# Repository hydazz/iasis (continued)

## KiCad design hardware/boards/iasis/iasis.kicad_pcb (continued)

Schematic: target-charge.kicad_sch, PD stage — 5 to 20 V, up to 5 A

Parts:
C1330, C1331, C1332, C1333, C1336, C1337, C1338, C1339: 10u 50V X7R; C_1210_3225Metric; MPN CL32B106KBJNNNE; LCSC C138687
C1334: 100u 35V; CP_Elec_6.3x7.7; MPN HBO101M1VTR-0608; LCSC C3031628
C1335, C1340, C1347, C1348: 100n 50V X7R; C_0402_1005Metric; MPN CL05B104KB54PNC; LCSC C307331
C1341, C1342: 100n; C_0402_1005Metric; MPN CL05B104KO5NNNC; LCSC C1525
C1343: 10u 16V X5R; C_0805_2012Metric; MPN CL21A106KAYNNNE; LCSC C15850
C1344: 10n; C_0402_1005Metric; MPN CL05B103KB5NNNC; LCSC C15195
C1345: 4.7n; C_0402_1005Metric; MPN 0402B472K500NT; LCSC C1538
C1346: 100p C0G; C_0402_1005Metric; MPN 0402CG101J500NT; LCSC C1546
L1330: 4.7u; L_Changjiang_FXL1050; MPN AAPS1050M4R7A; LCSC C54425770
NT1330: NetTie_2; NetTie-2_SMD_Pad0.5mm
Q1330, Q1331: TMGN4060DF; Vishay_PowerPAK_1212-8_Single; MPN TMGN4060DF; LCSC C7422903
Q1332, Q1333: SP60N05GNJ; Vishay_PowerPAK_1212-8_Single; MPN SP60N05GNJ; LCSC C22466768
Q1334: 2N7002; SOT-23; MPN 2N7002; LCSC C8545
R1330: 1; R_0402_1005Metric; MPN 0402WGF100KTCE; LCSC C25086
R1331, R1332, R1336: 47k 1%; R_0402_1005Metric; MPN 0402WGF4702TCE; LCSC C25792
R1333: 56k 1%; R_0402_1005Metric; MPN 0402WGF5602TCE; LCSC C25796
R1334: 10m 1%; R_1206_3216Metric; MPN RLM12FTCMR010; LCSC C188070
R1335: 200k 1%; R_0402_1005Metric; MPN 0402WGF2003TCE; LCSC C25764
R1337: 15k 1%; R_0402_1005Metric; MPN 0402WGF1502TCE; LCSC C25756
R1338, R1339: 100k; R_0402_1005Metric; MPN 0402WGF1003TCE; LCSC C25741
U1330: TPS55288RPMR; TI_RPM0026A; MPN TPS55288RPMR; LCSC C2864583
U1331: LM74502DDFR; Texas_DDF0008A_SOT-8_1.6x2.9mm_P0.65mm; MPN LM74502DDFR; LCSC C3236215

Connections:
5V_LOGIC: R1330.1; also elsewhere on the board
/Target ports/Target 2/Output and charging/CHARGE_EN: R1339.1, U1331.1 (EN); also elsewhere on the board
/Target ports/Target 2/Output and charging/Charging stage/CONV: C1334.1, C1347.2, C1348.1, Q1332.5 (D), R1334.2, R1335.1, U1330.13 (ISN), U1331.5 (VS)
/Target ports/Target 2/Output and charging/Charging stage/OUT_GATE: Q1332.4 (G), Q1333.4 (G), U1331.6 (GATE)
/Target ports/Target 2/Output and charging/Charging stage/OUT_OV: R1335.2, R1336.1, R1337.1, U1331.7 (OV)
/Target ports/Target 2/Output and charging/Charging stage/OUT_SRC: Q1332.1 (S), Q1332.2 (S), Q1332.3 (S), Q1333.1 (S), Q1333.2 (S), Q1333.3 (S), U1331.8 (SRC)
/Target ports/Target 2/Output and charging/Charging stage/STAGE_AGND: C1344.2, C1345.2, C1346.2, NT1330.2, R1331.2, R1332.2, U1330.10 (AGND)
/Target ports/Target 2/Output and charging/Charging stage/STAGE_COMP: C1346.1, R1333.1, U1330.18 (COMP)
/Target ports/Target 2/Output and charging/Charging stage/STAGE_DITH: C1344.1, U1330.7 (DITH_SYNC)
/Target ports/Target 2/Output and charging/Charging stage/STAGE_FSW: R1331.1, U1330.8 (FSW)
/Target ports/Target 2/Output and charging/Charging stage/STAGE_ILIM: R1332.1, U1330.17 (ILIM)
/Target ports/Target 2/Output and charging/Charging stage/STAGE_VCC: C1343.1, R1330.2, U1330.19 (VCC)
/Target ports/Target 2/Output and charging/Charging stage/STAGE_VOUT: C1336.1, C1337.1, C1338.1, C1339.1, C1340.1, R1334.1, U1330.11 (VOUT), U1330.12 (ISP), U1330.26 (VOUT)
/Target ports/Target 2/Output and charging/Charging stage/SW1: C1341.2, L1330.1, Q1330.1 (S), Q1330.2 (S), Q1330.3 (S), Q1331.5 (D), U1330.23 (SW1)
/Target ports/Target 2/Output and charging/Charging stage/SW2: C1342.2, L1330.2, U1330.21 (SW2), U1330.25 (SW2)
GND: C1330.2, C1331.2, C1332.2, C1333.2, C1334.2, C1335.2, C1336.2, C1337.2, C1338.2, C1339.2, C1340.2, C1343.2, C1348.2, NT1330.1, Q1331.1 (S), Q1331.2 (S), Q1331.3 (S), Q1334.2 (S), R1336.2, R1338.2, R1339.2, U1330.9 (PGND), U1330.24 (PGND), U1331.2 (GND); also elsewhere on the board
HV_CHARGE: C1330.1, C1331.1, C1332.1, C1333.1, C1335.1, Q1330.5 (D), U1330.3 (VIN); also elsewhere on the board
unnamed: C1345.1, R1333.2
unnamed: Q1330.4 (G), U1330.2 (DR1H)
unnamed: Q1331.4 (G), U1330.1 (DR1L)
unnamed: Q1334.3 (D), R1337.2
unnamed: C1341.1, U1330.22 (BOOT1)
unnamed: C1342.1, U1330.20 (BOOT2)
unnamed: C1347.1, U1331.4 (VCAP)
P2_OV_HIGH: Q1334.1 (G), R1338.1; also elsewhere on the board
P2_POWER_FAULT_N: U1330.14 (FB_INT); also elsewhere on the board
P2_SCL: U1330.5 (SCL); also elsewhere on the board
P2_SDA: U1330.6 (SDA); also elsewhere on the board
P2_VBUS: Q1333.5 (D); also elsewhere on the board
PD_STAGE_EN: U1330.4 (EN_UVLO); also elsewhere on the board

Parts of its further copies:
C1230, C1231, C1232, C1233, C1236, C1237, C1238, C1239, C1430, C1431, C1432, C1433, C1436, C1437, C1438, C1439, C1530, C1531, C1532, C1533, C1536, C1537, C1538, C1539, C1630, C1631, C1632, C1633, C1636, C1637, C1638, C1639: 10u 50V X7R; C_1210_3225Metric; MPN CL32B106KBJNNNE; LCSC C138687
C1234, C1434, C1534, C1634: 100u 35V; CP_Elec_6.3x7.7; MPN HBO101M1VTR-0608; LCSC C3031628
C1235, C1240, C1247, C1248, C1435, C1440, C1447, C1448, C1535, C1540, C1547, C1548, C1635, C1640, C1647, C1648: 100n 50V X7R; C_0402_1005Metric; MPN CL05B104KB54PNC; LCSC C307331
C1241, C1242, C1441, C1442, C1541, C1542, C1641, C1642: 100n; C_0402_1005Metric; MPN CL05B104KO5NNNC; LCSC C1525
C1243, C1443, C1543, C1643: 10u 16V X5R; C_0805_2012Metric; MPN CL21A106KAYNNNE; LCSC C15850
C1244, C1444, C1544, C1644: 10n; C_0402_1005Metric; MPN CL05B103KB5NNNC; LCSC C15195
C1245, C1445, C1545, C1645: 4.7n; C_0402_1005Metric; MPN 0402B472K500NT; LCSC C1538
C1246, C1446, C1546, C1646: 100p C0G; C_0402_1005Metric; MPN 0402CG101J500NT; LCSC C1546
L1230, L1430, L1530, L1630: 4.7u; L_Changjiang_FXL1050; MPN AAPS1050M4R7A; LCSC C54425770
NT1230, NT1430, NT1530, NT1630: NetTie_2; NetTie-2_SMD_Pad0.5mm
Q1230, Q1231, Q1430, Q1431, Q1530, Q1531, Q1630, Q1631: TMGN4060DF; Vishay_PowerPAK_1212-8_Single; MPN TMGN4060DF; LCSC C7422903
Q1232, Q1233, Q1432, Q1433, Q1532, Q1533, Q1632, Q1633: SP60N05GNJ; Vishay_PowerPAK_1212-8_Single; MPN SP60N05GNJ; LCSC C22466768
Q1234, Q1434, Q1534, Q1634: 2N7002; SOT-23; MPN 2N7002; LCSC C8545
R1230, R1430, R1530, R1630: 1; R_0402_1005Metric; MPN 0402WGF100KTCE; LCSC C25086
R1231, R1232, R1236, R1431, R1432, R1436, R1531, R1532, R1536, R1631, R1632, R1636: 47k 1%; R_0402_1005Metric; MPN 0402WGF4702TCE; LCSC C25792
R1233, R1433, R1533, R1633: 56k 1%; R_0402_1005Metric; MPN 0402WGF5602TCE; LCSC C25796
R1234, R1434, R1534, R1634: 10m 1%; R_1206_3216Metric; MPN RLM12FTCMR010; LCSC C188070
R1235, R1435, R1535, R1635: 200k 1%; R_0402_1005Metric; MPN 0402WGF2003TCE; LCSC C25764
R1237, R1437, R1537, R1637: 15k 1%; R_0402_1005Metric; MPN 0402WGF1502TCE; LCSC C25756
R1238, R1239, R1438, R1439, R1538, R1539, R1638, R1639: 100k; R_0402_1005Metric; MPN 0402WGF1003TCE; LCSC C25741
U1230, U1430, U1530, U1630: TPS55288RPMR; TI_RPM0026A; MPN TPS55288RPMR; LCSC C2864583
U1231, U1431, U1531, U1631: LM74502DDFR; Texas_DDF0008A_SOT-8_1.6x2.9mm_P0.65mm; MPN LM74502DDFR; LCSC C3236215

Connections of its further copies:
5V_LOGIC: R1230.1, R1430.1, R1530.1, R1630.1; also elsewhere on the board
/Target ports/Target 1/Output and charging/CHARGE_EN: R1239.1, U1231.1 (EN); also elsewhere on the board
/Target ports/Target 1/Output and charging/Charging stage/CONV: C1234.1, C1247.2, C1248.1, Q1232.5 (D), R1234.2, R1235.1, U1230.13 (ISN), U1231.5 (VS)
/Target ports/Target 1/Output and charging/Charging stage/OUT_GATE: Q1232.4 (G), Q1233.4 (G), U1231.6 (GATE)
/Target ports/Target 1/Output and charging/Charging stage/OUT_OV: R1235.2, R1236.1, R1237.1, U1231.7 (OV)
/Target ports/Target 1/Output and charging/Charging stage/OUT_SRC: Q1232.1 (S), Q1232.2 (S), Q1232.3 (S), Q1233.1 (S), Q1233.2 (S), Q1233.3 (S), U1231.8 (SRC)
/Target ports/Target 1/Output and charging/Charging stage/STAGE_AGND: C1244.2, C1245.2, C1246.2, NT1230.2, R1231.2, R1232.2, U1230.10 (AGND)
/Target ports/Target 1/Output and charging/Charging stage/STAGE_COMP: C1246.1, R1233.1, U1230.18 (COMP)
/Target ports/Target 1/Output and charging/Charging stage/STAGE_DITH: C1244.1, U1230.7 (DITH_SYNC)
/Target ports/Target 1/Output and charging/Charging stage/STAGE_FSW: R1231.1, U1230.8 (FSW)
/Target ports/Target 1/Output and charging/Charging stage/STAGE_ILIM: R1232.1, U1230.17 (ILIM)
/Target ports/Target 1/Output and charging/Charging stage/STAGE_VCC: C1243.1, R1230.2, U1230.19 (VCC)
/Target ports/Target 1/Output and charging/Charging stage/STAGE_VOUT: C1236.1, C1237.1, C1238.1, C1239.1, C1240.1, R1234.1, U1230.11 (VOUT), U1230.12 (ISP), U1230.26 (VOUT)
/Target ports/Target 1/Output and charging/Charging stage/SW1: C1241.2, L1230.1, Q1230.1 (S), Q1230.2 (S), Q1230.3 (S), Q1231.5 (D), U1230.23 (SW1)
/Target ports/Target 1/Output and charging/Charging stage/SW2: C1242.2, L1230.2, U1230.21 (SW2), U1230.25 (SW2)
/Target ports/Target 3/Output and charging/CHARGE_EN: R1439.1, U1431.1 (EN); also elsewhere on the board
/Target ports/Target 3/Output and charging/Charging stage/CONV: C1434.1, C1447.2, C1448.1, Q1432.5 (D), R1434.2, R1435.1, U1430.13 (ISN), U1431.5 (VS)
/Target ports/Target 3/Output and charging/Charging stage/OUT_GATE: Q1432.4 (G), Q1433.4 (G), U1431.6 (GATE)
/Target ports/Target 3/Output and charging/Charging stage/OUT_OV: R1435.2, R1436.1, R1437.1, U1431.7 (OV)
/Target ports/Target 3/Output and charging/Charging stage/OUT_SRC: Q1432.1 (S), Q1432.2 (S), Q1432.3 (S), Q1433.1 (S), Q1433.2 (S), Q1433.3 (S), U1431.8 (SRC)
/Target ports/Target 3/Output and charging/Charging stage/STAGE_AGND: C1444.2, C1445.2, C1446.2, NT1430.2, R1431.2, R1432.2, U1430.10 (AGND)
/Target ports/Target 3/Output and charging/Charging stage/STAGE_COMP: C1446.1, R1433.1, U1430.18 (COMP)
/Target ports/Target 3/Output and charging/Charging stage/STAGE_DITH: C1444.1, U1430.7 (DITH_SYNC)
/Target ports/Target 3/Output and charging/Charging stage/STAGE_FSW: R1431.1, U1430.8 (FSW)
/Target ports/Target 3/Output and charging/Charging stage/STAGE_ILIM: R1432.1, U1430.17 (ILIM)
/Target ports/Target 3/Output and charging/Charging stage/STAGE_VCC: C1443.1, R1430.2, U1430.19 (VCC)
/Target ports/Target 3/Output and charging/Charging stage/STAGE_VOUT: C1436.1, C1437.1, C1438.1, C1439.1, C1440.1, R1434.1, U1430.11 (VOUT), U1430.12 (ISP), U1430.26 (VOUT)
/Target ports/Target 3/Output and charging/Charging stage/SW1: C1441.2, L1430.1, Q1430.1 (S), Q1430.2 (S), Q1430.3 (S), Q1431.5 (D), U1430.23 (SW1)
/Target ports/Target 3/Output and charging/Charging stage/SW2: C1442.2, L1430.2, U1430.21 (SW2), U1430.25 (SW2)
/Target ports/Target 4/Output and charging/CHARGE_EN: R1539.1, U1531.1 (EN); also elsewhere on the board
/Target ports/Target 4/Output and charging/Charging stage/CONV: C1534.1, C1547.2, C1548.1, Q1532.5 (D), R1534.2, R1535.1, U1530.13 (ISN), U1531.5 (VS)
/Target ports/Target 4/Output and charging/Charging stage/OUT_GATE: Q1532.4 (G), Q1533.4 (G), U1531.6 (GATE)
/Target ports/Target 4/Output and charging/Charging stage/OUT_OV: R1535.2, R1536.1, R1537.1, U1531.7 (OV)
/Target ports/Target 4/Output and charging/Charging stage/OUT_SRC: Q1532.1 (S), Q1532.2 (S), Q1532.3 (S), Q1533.1 (S), Q1533.2 (S), Q1533.3 (S), U1531.8 (SRC)
/Target ports/Target 4/Output and charging/Charging stage/STAGE_AGND: C1544.2, C1545.2, C1546.2, NT1530.2, R1531.2, R1532.2, U1530.10 (AGND)
/Target ports/Target 4/Output and charging/Charging stage/STAGE_COMP: C1546.1, R1533.1, U1530.18 (COMP)
/Target ports/Target 4/Output and charging/Charging stage/STAGE_DITH: C1544.1, U1530.7 (DITH_SYNC)
/Target ports/Target 4/Output and charging/Charging stage/STAGE_FSW: R1531.1, U1530.8 (FSW)
/Target ports/Target 4/Output and charging/Charging stage/STAGE_ILIM: R1532.1, U1530.17 (ILIM)
/Target ports/Target 4/Output and charging/Charging stage/STAGE_VCC: C1543.1, R1530.2, U1530.19 (VCC)
/Target ports/Target 4/Output and charging/Charging stage/STAGE_VOUT: C1536.1, C1537.1, C1538.1, C1539.1, C1540.1, R1534.1, U1530.11 (VOUT), U1530.12 (ISP), U1530.26 (VOUT)
/Target ports/Target 4/Output and charging/Charging stage/SW1: C1541.2, L1530.1, Q1530.1 (S), Q1530.2 (S), Q1530.3 (S), Q1531.5 (D), U1530.23 (SW1)
/Target ports/Target 4/Output and charging/Charging stage/SW2: C1542.2, L1530.2, U1530.21 (SW2), U1530.25 (SW2)
/Target ports/Target 5/Output and charging/CHARGE_EN: R1639.1, U1631.1 (EN); also elsewhere on the board
/Target ports/Target 5/Output and charging/Charging stage/CONV: C1634.1, C1647.2, C1648.1, Q1632.5 (D), R1634.2, R1635.1, U1630.13 (ISN), U1631.5 (VS)
/Target ports/Target 5/Output and charging/Charging stage/OUT_GATE: Q1632.4 (G), Q1633.4 (G), U1631.6 (GATE)
/Target ports/Target 5/Output and charging/Charging stage/OUT_OV: R1635.2, R1636.1, R1637.1, U1631.7 (OV)
/Target ports/Target 5/Output and charging/Charging stage/OUT_SRC: Q1632.1 (S), Q1632.2 (S), Q1632.3 (S), Q1633.1 (S), Q1633.2 (S), Q1633.3 (S), U1631.8 (SRC)
/Target ports/Target 5/Output and charging/Charging stage/STAGE_AGND: C1644.2, C1645.2, C1646.2, NT1630.2, R1631.2, R1632.2, U1630.10 (AGND)
/Target ports/Target 5/Output and charging/Charging stage/STAGE_COMP: C1646.1, R1633.1, U1630.18 (COMP)
/Target ports/Target 5/Output and charging/Charging stage/STAGE_DITH: C1644.1, U1630.7 (DITH_SYNC)
/Target ports/Target 5/Output and charging/Charging stage/STAGE_FSW: R1631.1, U1630.8 (FSW)
/Target ports/Target 5/Output and charging/Charging stage/STAGE_ILIM: R1632.1, U1630.17 (ILIM)
/Target ports/Target 5/Output and charging/Charging stage/STAGE_VCC: C1643.1, R1630.2, U1630.19 (VCC)
/Target ports/Target 5/Output and charging/Charging stage/STAGE_VOUT: C1636.1, C1637.1, C1638.1, C1639.1, C1640.1, R1634.1, U1630.11 (VOUT), U1630.12 (ISP), U1630.26 (VOUT)
/Target ports/Target 5/Output and charging/Charging stage/SW1: C1641.2, L1630.1, Q1630.1 (S), Q1630.2 (S), Q1630.3 (S), Q1631.5 (D), U1630.23 (SW1)
/Target ports/Target 5/Output and charging/Charging stage/SW2: C1642.2, L1630.2, U1630.21 (SW2), U1630.25 (SW2)
GND: C1230.2, C1231.2, C1232.2, C1233.2, C1234.2, C1235.2, C1236.2, C1237.2, C1238.2, C1239.2, C1240.2, C1243.2, C1248.2, C1430.2, C1431.2, C1432.2, C1433.2, C1434.2, C1435.2, C1436.2, C1437.2, C1438.2, C1439.2, C1440.2, C1443.2, C1448.2, C1530.2, C1531.2, C1532.2, C1533.2, C1534.2, C1535.2, C1536.2, C1537.2, C1538.2, C1539.2, C1540.2, C1543.2, C1548.2, C1630.2, C1631.2, C1632.2, C1633.2, C1634.2, C1635.2, C1636.2, C1637.2, C1638.2, C1639.2, C1640.2, C1643.2, C1648.2, NT1230.1, NT1430.1, NT1530.1, NT1630.1, Q1231.1 (S), Q1231.2 (S), Q1231.3 (S), Q1234.2 (S), Q1431.1 (S), Q1431.2 (S), Q1431.3 (S), Q1434.2 (S), Q1531.1 (S), Q1531.2 (S), Q1531.3 (S), Q1534.2 (S), Q1631.1 (S), Q1631.2 (S), Q1631.3 (S), Q1634.2 (S), R1236.2, R1238.2, R1239.2, R1436.2, R1438.2, R1439.2, R1536.2, R1538.2, R1539.2, R1636.2, R1638.2, R1639.2, U1230.9 (PGND), U1230.24 (PGND), U1231.2 (GND), U1430.9 (PGND), U1430.24 (PGND), U1431.2 (GND), U1530.9 (PGND), U1530.24 (PGND), U1531.2 (GND), U1630.9 (PGND), U1630.24 (PGND), U1631.2 (GND); also elsewhere on the board
HV_CHARGE: C1230.1, C1231.1, C1232.1, C1233.1, C1235.1, C1430.1, C1431.1, C1432.1, C1433.1, C1435.1, C1530.1, C1531.1, C1532.1, C1533.1, C1535.1, C1630.1, C1631.1, C1632.1, C1633.1, C1635.1, Q1230.5 (D), Q1430.5 (D), Q1530.5 (D), Q1630.5 (D), U1230.3 (VIN), U1430.3 (VIN), U1530.3 (VIN), U1630.3 (VIN); also elsewhere on the board
unnamed: C1245.1, R1233.2
unnamed: C1445.1, R1433.2
unnamed: C1545.1, R1533.2
unnamed: C1645.1, R1633.2
unnamed: Q1230.4 (G), U1230.2 (DR1H)
unnamed: Q1231.4 (G), U1230.1 (DR1L)
unnamed: Q1234.3 (D), R1237.2
unnamed: Q1430.4 (G), U1430.2 (DR1H)
unnamed: Q1431.4 (G), U1430.1 (DR1L)
unnamed: Q1434.3 (D), R1437.2
unnamed: Q1530.4 (G), U1530.2 (DR1H)
unnamed: Q1531.4 (G), U1530.1 (DR1L)
unnamed: Q1534.3 (D), R1537.2
unnamed: Q1630.4 (G), U1630.2 (DR1H)
unnamed: Q1631.4 (G), U1630.1 (DR1L)
unnamed: Q1634.3 (D), R1637.2
unnamed: C1241.1, U1230.22 (BOOT1)
unnamed: C1242.1, U1230.20 (BOOT2)
unnamed: C1247.1, U1231.4 (VCAP)
unnamed: C1441.1, U1430.22 (BOOT1)
unnamed: C1442.1, U1430.20 (BOOT2)
unnamed: C1447.1, U1431.4 (VCAP)
unnamed: C1541.1, U1530.22 (BOOT1)
unnamed: C1542.1, U1530.20 (BOOT2)
unnamed: C1547.1, U1531.4 (VCAP)
unnamed: C1641.1, U1630.22 (BOOT1)
unnamed: C1642.1, U1630.20 (BOOT2)
unnamed: C1647.1, U1631.4 (VCAP)
P1_OV_HIGH: Q1234.1 (G), R1238.1; also elsewhere on the board
P1_POWER_FAULT_N: U1230.14 (FB_INT); also elsewhere on the board
P1_SCL: U1230.5 (SCL); also elsewhere on the board
P1_SDA: U1230.6 (SDA); also elsewhere on the board
P1_VBUS: Q1233.5 (D); also elsewhere on the board
P3_OV_HIGH: Q1434.1 (G), R1438.1; also elsewhere on the board
P3_POWER_FAULT_N: U1430.14 (FB_INT); also elsewhere on the board
P3_SCL: U1430.5 (SCL); also elsewhere on the board
P3_SDA: U1430.6 (SDA); also elsewhere on the board
P3_VBUS: Q1433.5 (D); also elsewhere on the board
P4_OV_HIGH: Q1534.1 (G), R1538.1; also elsewhere on the board
P4_POWER_FAULT_N: U1530.14 (FB_INT); also elsewhere on the board
P4_SCL: U1530.5 (SCL); also elsewhere on the board
P4_SDA: U1530.6 (SDA); also elsewhere on the board
P4_VBUS: Q1533.5 (D); also elsewhere on the board
P5_OV_HIGH: Q1634.1 (G), R1638.1; also elsewhere on the board
P5_POWER_FAULT_N: U1630.14 (FB_INT); also elsewhere on the board
P5_SCL: U1630.5 (SCL); also elsewhere on the board
P5_SDA: U1630.6 (SDA); also elsewhere on the board
P5_VBUS: Q1633.5 (D); also elsewhere on the board
PD_STAGE_EN: U1230.4 (EN_UVLO), U1430.4 (EN_UVLO), U1530.4 (EN_UVLO), U1630.4 (EN_UVLO); also elsewhere on the board

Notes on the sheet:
PD stage — 5 to 20 V, up to 5 A
TPS55288 at I2C 0x75 on the port channel (MODE open: external VCC, PFM). OE defaults off; EN low resets the registers. FSW 47k: 425 kHz. ILIM 47k: 7.0 A average inductor limit. Output limit via 10 mOhm sense, up to 6.35 A by register. Output switch: LM74502 with back-to-back FETs; OV trips at 6.6 V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

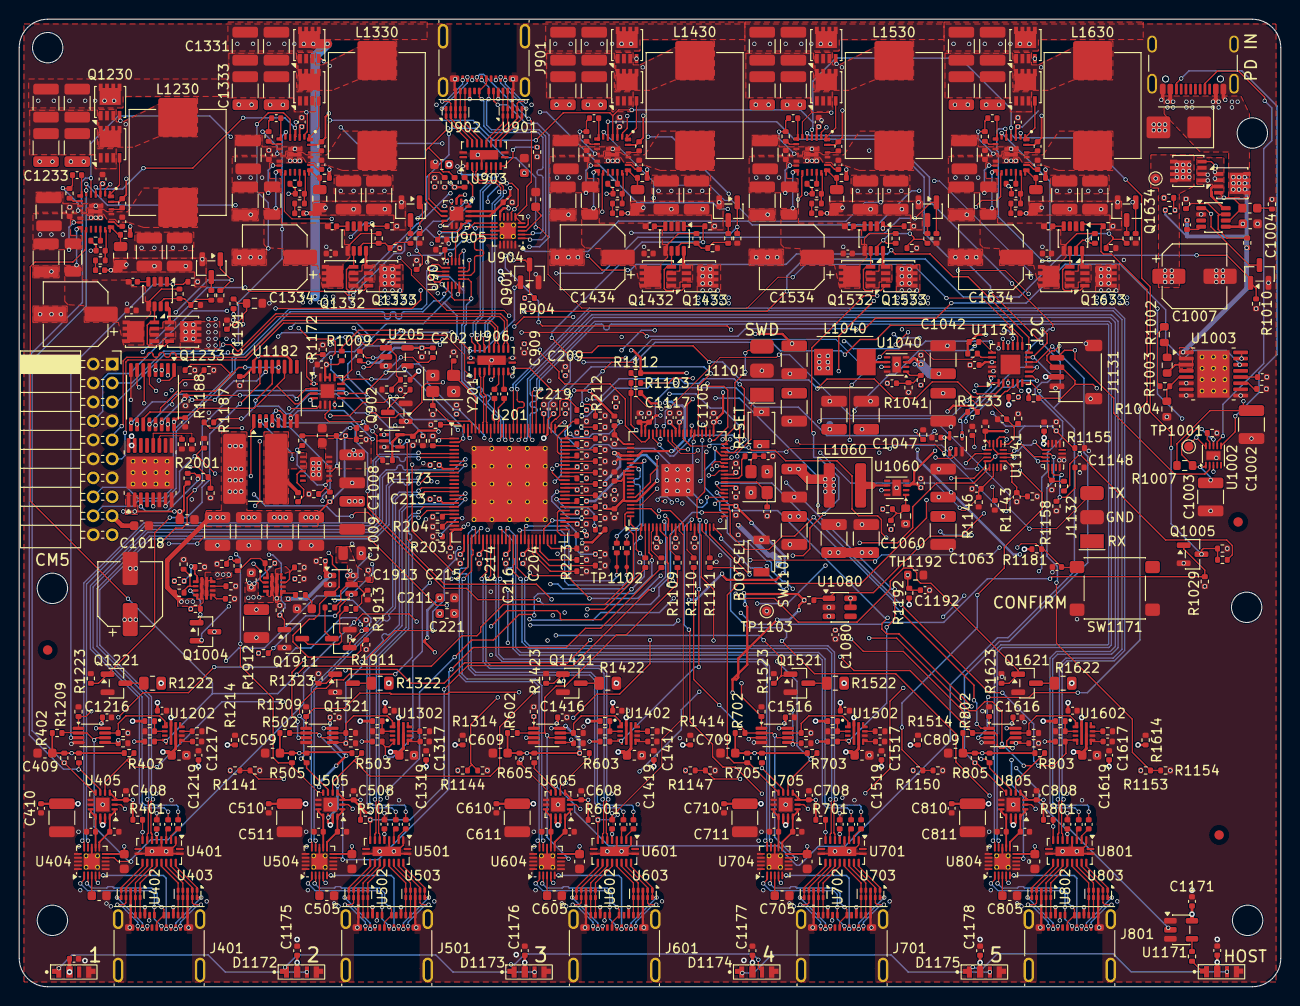
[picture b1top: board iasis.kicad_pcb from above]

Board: 6 copper layers, 133.0 x 102.0 mm, 723 parts (0 on the bottom side), 494 nets.

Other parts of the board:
FID1, FID2, FID3: Fiducial; Fiducial_1mm_Mask2mm
H1, H2, H3, H4, H5, H6: MountingHole_3.2mm_M3

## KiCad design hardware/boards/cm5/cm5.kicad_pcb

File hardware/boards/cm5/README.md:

# CM5 carrier

An optional Raspberry Pi Compute Module 5 carrier for Iasis. It plugs into the main board's side socket and carries Ethernet, NVMe storage, an accessory USB-C port and a service USB-C port. The [CM5 case](../../case/README.md#cm5-assembly) holds both boards.

## Parts and power

| Item                      | Requirement or limit                                       |
| ------------------------- | ---------------------------------------------------------- |
| Main board                | Default population, with the side socket and its feed      |
| Input                     | USB-C PD supply offering 20 V, connected to the main board |
| Storage                   | eMMC on the module, or NVMe for CM5 Lite; no microSD slot  |
| NVMe SSD                  | M-key, 2230 / 2242 / 2280, up to 6 W                       |
| Fan                       | Up to 0.4 A; rated to tolerate 5.19 V                      |
| RTC backup                | Raspberry Pi RTC Battery SC1163, rechargeable ML2020       |
| Accessory USB-C           | 5 V / 1.5 A                                                |
| Carrier power reservation | 35 W including conversion losses and VCONN                 |

The service port is for CM5 provisioning and recovery; power comes through the main board. Set [`PSU_MAX_CURRENT=5000`](https://www.raspberrypi.com/documentation/computers/raspberry-pi.html#PSU_MAX_CURRENT) in the CM5 EEPROM configuration for the accessory USB allowance.

## RTC battery

Connect the battery to J104. To enable charging, add this to `/boot/firmware/config.txt` and reboot:

```ini
dtparam=rtc_bbat_vchg=3000000
```

Use this setting only with the specified rechargeable battery. See [Raspberry Pi's RTC setup](https://www.raspberrypi.com/documentation/computers/raspberry-pi.html#enable-battery-charging) for diagnostics.

## Fabrication

With the [development tools](../../../README.md#build) installed:

```sh
mise run //hardware/boards/cm5:lint
mise run //hardware/boards/cm5:fab
```

`build/boards/cm5/` contains `gerbers.zip`, `bom.csv` and `cpl.csv`. The board is 75.1 × 102 mm and uses the [main board's six-layer ordering settings](../iasis/README.md#jlcpcb-order). Select its accessory and service USB-C connectors (`J401`, `J501`) in the assembly order.

Use `:step` for the populated STEP and `:preview` for `board.png`. `version.txt` holds the board's version, which the title blocks and the silkscreen print. Each ordered version is a release tagged `cm5-board-v<version>` with its fabrication files attached.

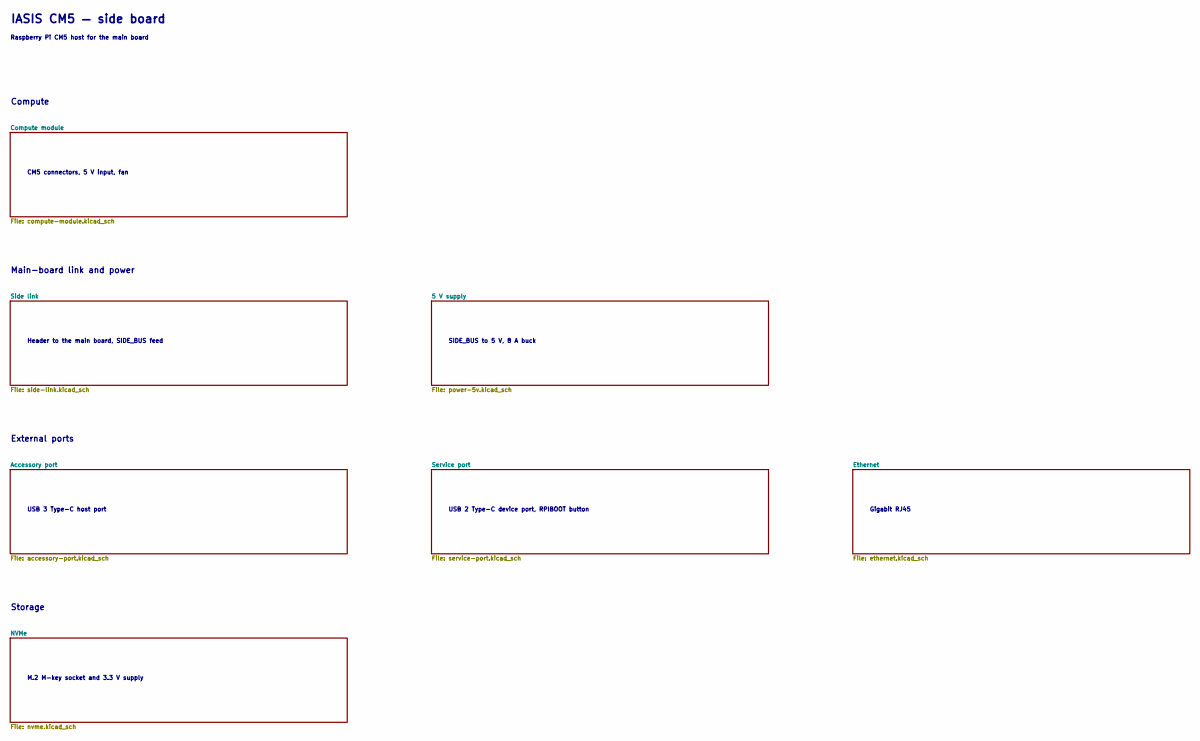
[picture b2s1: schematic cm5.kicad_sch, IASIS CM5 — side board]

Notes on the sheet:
Compute
CM5 connectors, 5 V input, fan
Main-board link and power
Header to the main board, SIDE_BUS feed
SIDE_BUS to 5 V, 8 A buck
External ports
USB 3 Type-C host port
USB 2 Type-C device port, RPIBOOT button
Gigabit RJ45
Storage
M.2 M-key socket and 3.3 V supply
IASIS CM5 — side board
Raspberry Pi CM5 host for the main board

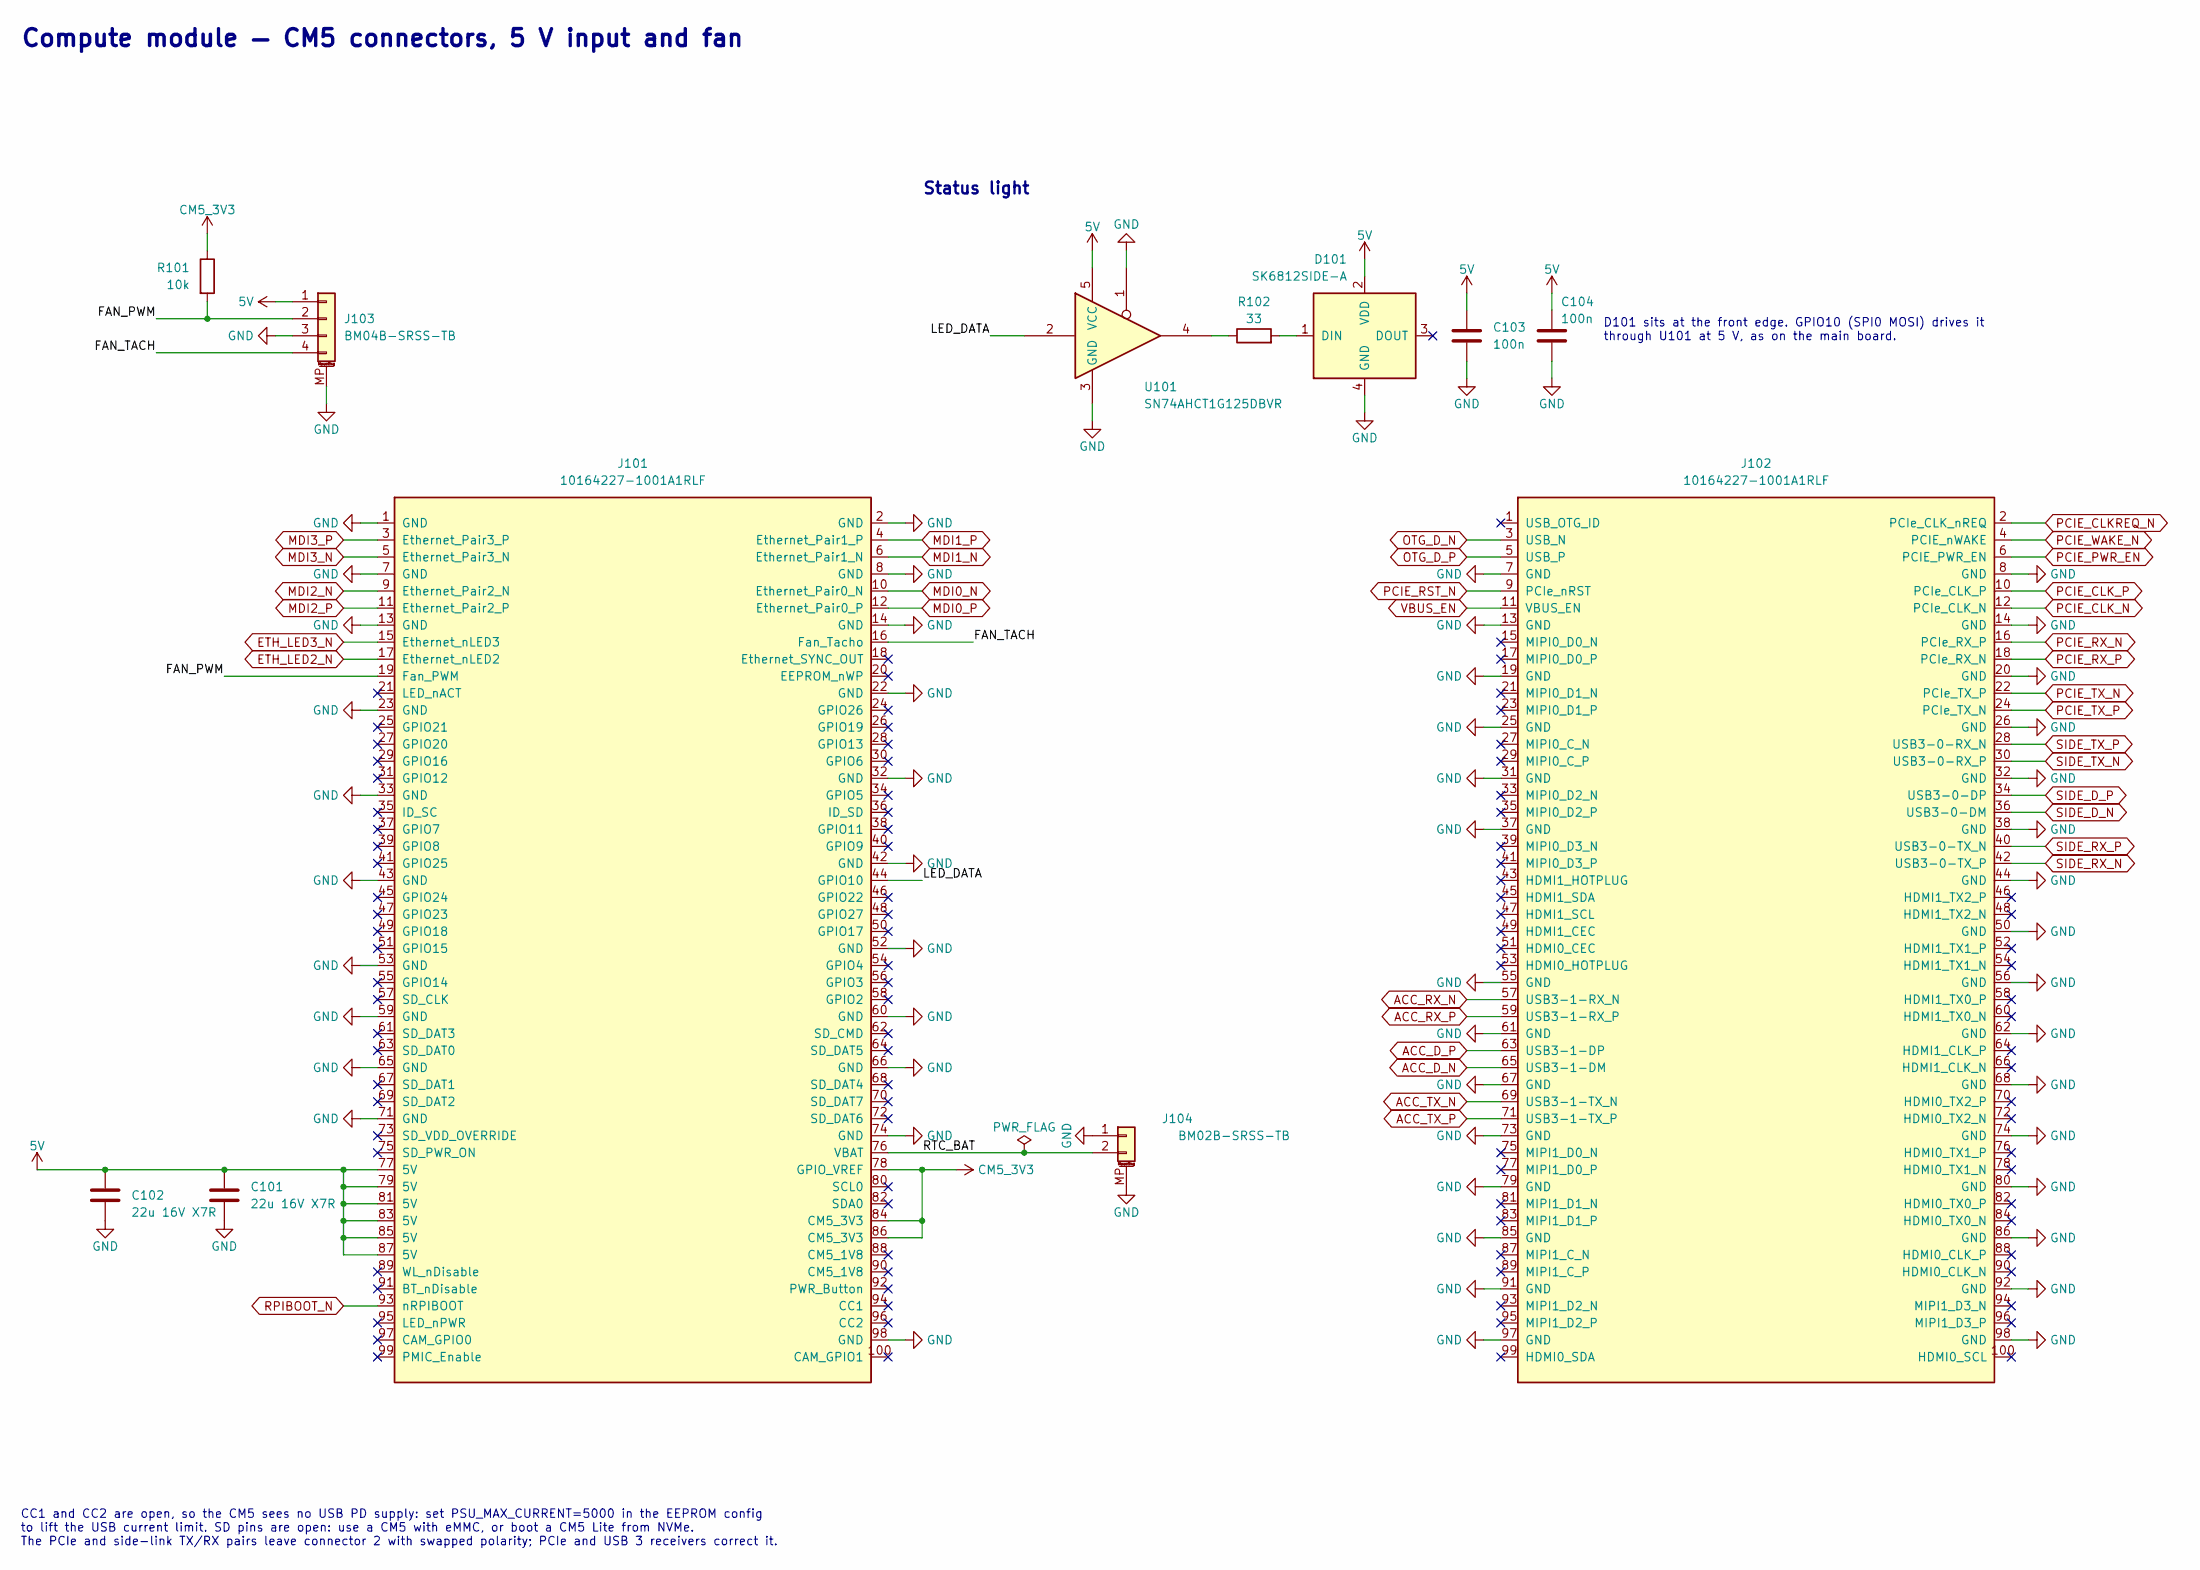
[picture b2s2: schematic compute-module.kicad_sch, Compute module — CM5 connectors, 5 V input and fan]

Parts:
C101, C102: 22u 16V X7R; C_1210_3225Metric; MPN CL32B226KOJNNNE; LCSC C55530
C103, C104: 100n; C_0402_1005Metric; MPN CL05B104KO5NNNC; LCSC C1525
D101: SK6812SIDE-A; OPSCO_SK6812SIDE-A; MPN SK6812SIDE-A; LCSC C5378721
J101, J102: 10164227-1001A1RLF; Hirose_DF40C-100DS-0.4V_2x50_P0.4mm; MPN 10164227-1001A1RLF; LCSC C6782225
J103: BM04B-SRSS-TB; JST_SH_BM04B-SRSS-TB_1x04-1MP_P1.00mm_Vertical; MPN BM04B-SRSS-TB(LF)(SN); LCSC C160390
J104: BM02B-SRSS-TB; JST_SH_BM02B-SRSS-TB_1x02-1MP_P1.00mm_Vertical; MPN BM02B-SRSS-TB(LF)(SN); LCSC C160388
R101: 10k; R_0402_1005Metric; MPN 0402WGF1002TCE; LCSC C25744
R102: 33; R_0402_1005Metric; MPN 0402WGF330JTCE; LCSC C25105
U101: SN74AHCT1G125DBVR; SOT-23-5; MPN SN74AHCT1G125DBVR; LCSC C7484

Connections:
5V: C101.1, C102.1, C103.1, C104.1, D101.2 (VDD), J101.77 (5V), J101.79 (5V), J101.81 (5V), J101.83 (5V), J101.85 (5V), J101.87 (5V), J103.1, U101.5 (VCC); also elsewhere on the board
/Compute module/FAN_PWM: J101.19 (Fan_PWM), J103.2, R101.2
/Compute module/FAN_TACH: J101.16 (Fan_Tacho), J103.4
/Compute module/LED_DATA: J101.44 (GPIO10), U101.2
/Compute module/RTC_BAT: J101.76 (VBAT), J104.2
ACC_D_N: J102.65 (USB3-1-DM); also elsewhere on the board
ACC_D_P: J102.63 (USB3-1-DP); also elsewhere on the board
ACC_RX_N: J102.57 (USB3-1-RX_N); also elsewhere on the board
ACC_RX_P: J102.59 (USB3-1-RX_P); also elsewhere on the board
ACC_TX_N: J102.69 (USB3-1-TX_N); also elsewhere on the board
ACC_TX_P: J102.71 (USB3-1-TX_P); also elsewhere on the board
CM5_3V3: J101.78 (GPIO_VREF), J101.84 (CM5_3V3), J101.86 (CM5_3V3), R101.1; also elsewhere on the board
ETH_LED2_N: J101.17 (Ethernet_nLED2); also elsewhere on the board
ETH_LED3_N: J101.15 (Ethernet_nLED3); also elsewhere on the board
GND: C101.2, C102.2, C103.2, C104.2, D101.4 (GND), J101.1 (GND), J101.2 (GND), J101.7 (GND), J101.8 (GND), J101.13 (GND), J101.14 (GND), J101.22 (GND), J101.23 (GND), J101.32 (GND), J101.33 (GND), J101.42 (GND), J101.43 (GND), J101.52 (GND), J101.53 (GND), J101.59 (GND), J101.60 (GND), J101.65 (GND), J101.66 (GND), J101.71 (GND), J101.74 (GND), J101.98 (GND), J102.7 (GND), J102.8 (GND), J102.13 (GND), J102.14 (GND), J102.19 (GND), J102.20 (GND), J102.25 (GND), J102.26 (GND), J102.31 (GND), J102.32 (GND), J102.37 (GND), J102.38 (GND), J102.44 (GND), J102.50 (GND), J102.55 (GND), J102.56 (GND), J102.61 (GND), J102.62 (GND), J102.67 (GND), J102.68 (GND), J102.73 (GND), J102.74 (GND), J102.79 (GND), J102.80 (GND), J102.85 (GND), J102.86 (GND), J102.91 (GND), J102.92 (GND), J102.97 (GND), J102.98 (GND), J103.3, J103.MP (MountPin), J104.1, J104.MP (MountPin), U101.1, U101.3 (GND); also elsewhere on the board
MDI0_N: J101.10 (Ethernet_Pair0_N); also elsewhere on the board
MDI0_P: J101.12 (Ethernet_Pair0_P); also elsewhere on the board
MDI1_N: J101.6 (Ethernet_Pair1_N); also elsewhere on the board
MDI1_P: J101.4 (Ethernet_Pair1_P); also elsewhere on the board
MDI2_N: J101.9 (Ethernet_Pair2_N); also elsewhere on the board
MDI2_P: J101.11 (Ethernet_Pair2_P); also elsewhere on the board
MDI3_N: J101.5 (Ethernet_Pair3_N); also elsewhere on the board
MDI3_P: J101.3 (Ethernet_Pair3_P); also elsewhere on the board
unnamed: D101.1 (DIN), R102.2
unnamed: R102.1, U101.4
OTG_D_N: J102.3 (USB_N); also elsewhere on the board
OTG_D_P: J102.5 (USB_P); also elsewhere on the board
PCIE_CLKREQ_N: J102.2 (PCIe_CLK_nREQ); also elsewhere on the board
PCIE_CLK_N: J102.12 (PCIe_CLK_N); also elsewhere on the board
PCIE_CLK_P: J102.10 (PCIe_CLK_P); also elsewhere on the board
PCIE_PWR_EN: J102.6 (PCIE_PWR_EN); also elsewhere on the board
PCIE_RST_N: J102.9 (PCIe_nRST); also elsewhere on the board
PCIE_RX_N: J102.16 (PCIe_RX_P); also elsewhere on the board
PCIE_RX_P: J102.18 (PCIe_RX_N); also elsewhere on the board
PCIE_TX_N: J102.22 (PCIe_TX_P); also elsewhere on the board
PCIE_TX_P: J102.24 (PCIe_TX_N); also elsewhere on the board
PCIE_WAKE_N: J102.4 (PCIE_nWAKE); also elsewhere on the board
RPIBOOT_N: J101.93 (nRPIBOOT); also elsewhere on the board
SIDE_D_N: J102.36 (USB3-0-DM); also elsewhere on the board
SIDE_D_P: J102.34 (USB3-0-DP); also elsewhere on the board
SIDE_RX_N: J102.42 (USB3-0-TX_P); also elsewhere on the board
SIDE_RX_P: J102.40 (USB3-0-TX_N); also elsewhere on the board
SIDE_TX_N: J102.30 (USB3-0-RX_P); also elsewhere on the board
SIDE_TX_P: J102.28 (USB3-0-RX_N); also elsewhere on the board
VBUS_EN: J102.11 (VBUS_EN); also elsewhere on the board

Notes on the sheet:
Compute module — CM5 connectors, 5 V input and fan
CC1 and CC2 are open, so the CM5 sees no USB PD supply: set PSU_MAX_CURRENT=5000 in the EEPROM config to lift the USB current limit. SD pins are open: use a CM5 with eMMC, or boot a CM5 Lite from NVMe. The PCIe and side-link TX/RX pairs leave connector 2 with swapped polarity; PCIe and USB 3 receiv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
Status light
D101 sits at the front edge. GPIO10 (SPI0 MOSI) drives it through U101 at 5 V, as on the main board.

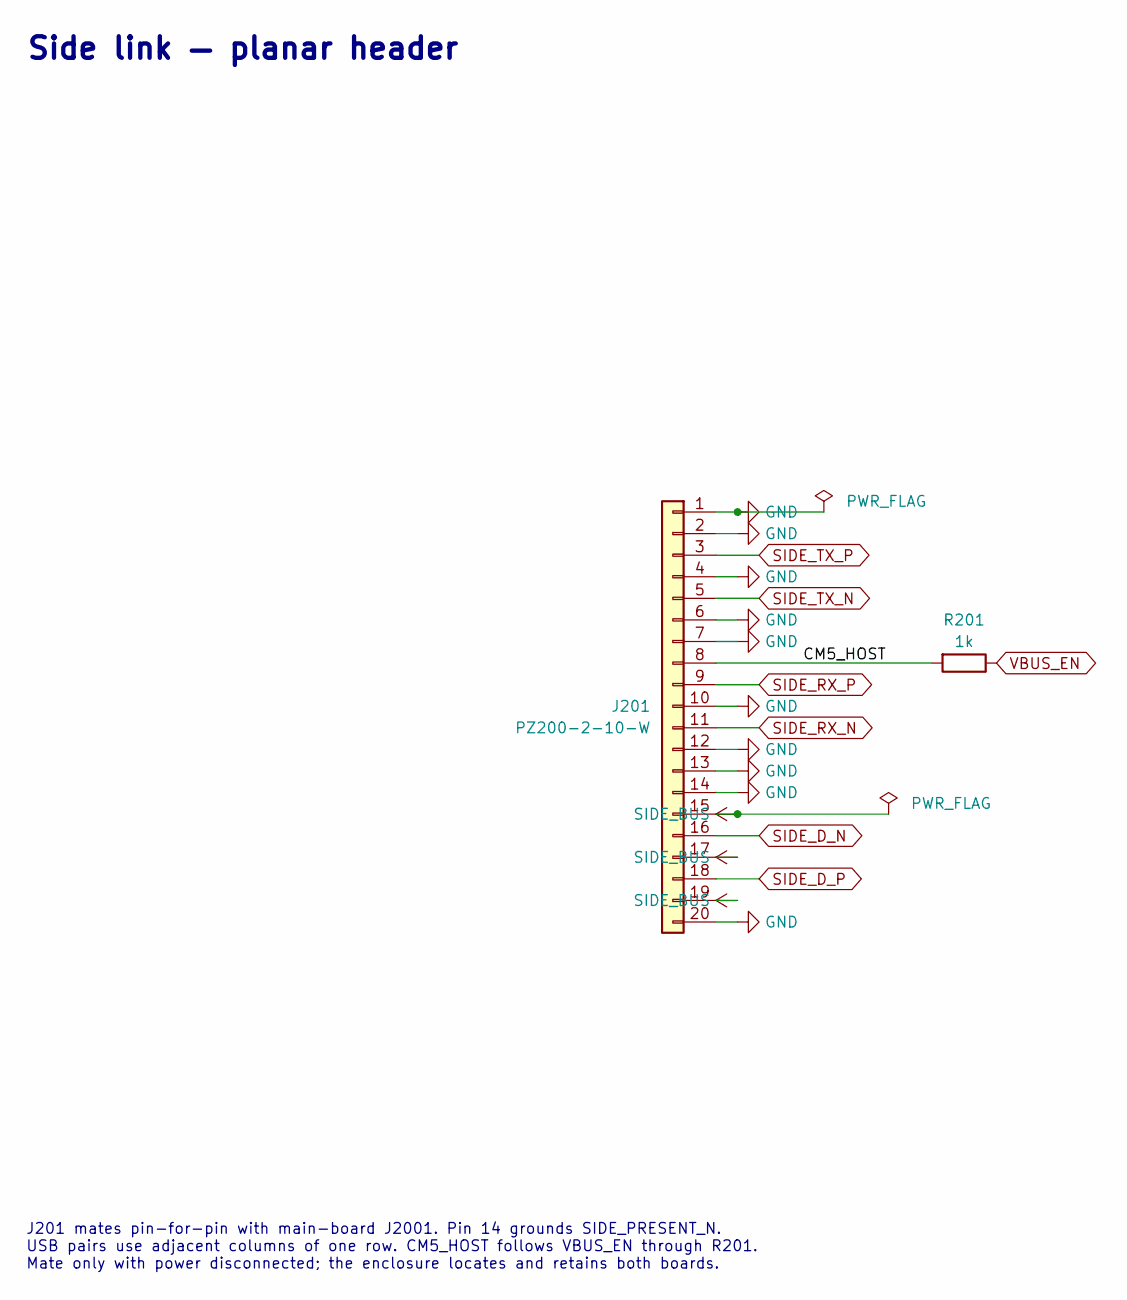
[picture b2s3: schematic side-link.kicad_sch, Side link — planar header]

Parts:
J201: PZ200-2-10-W; PinHeader_2x10_P2.00mm_Horizontal; MPN PZ200-2-10-W; LCSC C2906016
R201: 1k; R_0402_1005Metric; MPN 0402WGF1001TCE; LCSC C11702

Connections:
/Side link/CM5_HOST: J201.8, R201.2
GND: J201.1, J201.2, J201.4, J201.6, J201.7, J201.10, J201.12, J201.13, J201.14, J201.20; also elsewhere on the board
SIDE_BUS: J201.15, J201.17, J201.19; also elsewhere on the board
SIDE_D_N: J201.16; also elsewhere on the board
SIDE_D_P: J201.18; also elsewhere on the board
SIDE_RX_N: J201.11; also elsewhere on the board
SIDE_RX_P: J201.9; also elsewhere on the board
SIDE_TX_N: J201.5; also elsewhere on the board
SIDE_TX_P: J201.3; also elsewhere on the board
VBUS_EN: R201.1; also elsewhere on the board

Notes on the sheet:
Side link — planar header
J201 mates pin-for-pin with main-board J2001. Pin 14 grounds SIDE_PRESENT_N. USB pairs use adjacent columns of one row. CM5_HOST follows VBUS_EN through R201. Mate only with power disconnected; the enclosure locates and retains both boards.
